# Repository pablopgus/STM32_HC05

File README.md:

# STM32_HC05
This is a PCB board designed in KiCAD which implements a STM32F746VGT6 microcontroller exposing the following pins and internal connections. All of the GPIO pins support timer peripheral output, for a more detailed view of the potential PIN function, check the STM32F7 datasheet using name as a reference. Please read [STM32F7 Reference page](https://www.st.com/en/microcontrollers-microprocessors/stm32f7-series.html) and [Getting Started Guide](https://www.st.com/resource/en/user_manual/dm00180213-getting-started-with-stm32cubef7-mcu-package-for-stm32f7-series-stmicroelectronics.pdf).

This board includes a [HC-05 Bluetooth module](https://components101.com/wireless/hc-05-bluetooth-module)  which exposes a serial port interface over bluetooth as a direct link with the microcontroller. The bluetooth module is switched on/off with a transistor switch controlled by a microcontroller pin. 

## Board Design

## Pinout

## Pin Function

| Name            | Pin     | Extra Functions   |
| :-------------: |:-------:| :-------------:   |
| PA0             | 22      | ADC0, UART4_TX, USART2_CTS |
| PA1             | 23      | ADC1, UART4_RX, USART2_RTS |
| PA2             | 24      | ADC2, USART2_TX            |
| PA3             | 25      | ADC3, USART2_RX            |
| PA4             | 28      | ADC4, USART2_CLK           |
| PA5             | 29      | ADC5, SPI1_CLK             |
| PA6             | 30      | ADC6, SPI1_MISO            |
| PA7             | 31      | ADC7, SPI1_MOSI            |
| PB0             | 34      | ADC8                       |
| PB1             | 35      | ADC9                       |
| PB10            | 46      | I2C2_CLK                   |
| PB11            | 47      | I2C2_SDA                   |
| PD8             | 55      | USART3_TX                  |
| PD9             | 56      | USART3_RX                  |
| PD10            | 57      | USART3_CLK                 |
| PD11            | 58      | USART3_CTS                 |
| PD12            | 59      | USART3_RTS                 |
| PD13            | 60      |                            |
| PD14            | 61      |                            |
| PD15            | 62      |                            |
| PD0             | 81      | Green LED                  |
| PD1             | 82      | Red LED                    |
| PD2             | 83      | Blue LED                   |
| PD3             | 84      | Orange LED                 |
| PD4             | 85      | Yellow LED                 |
| PC6             | 63      | HC-05 UART RX              |
| PC7             | 64      | HC-05 UART TX              |
| PC8             | 65      | HC-05 BT KEY               |
| PE12            | 42      | Bluetooth Enable           |

## Programming Interface
The programming and power port is located on the upper left section of the board. The flashing debugging must be performed using a ST-Link/v2 debugger or STM32FX evaluation board (Discovery, Nucleo, etc ...). LEDs are connected to GPIO (PD0-4), bluetooth module is connected to UART6 port and the bluetooth module on/off actuation is driven by GPIO PE12. Further information on programming and the specific pin functions can be found on the STM32F7 datasheet, and the HC-05 bluetooth module reference guide.

# Code Examples
The following 4 files form the required interface to program and operate the Bluetooth module via the UART peripheral of the STM32F7.
## bluetooth.h
```C
#ifndef __bluetooth_H
#define __bluetooth_H
#ifdef __cplusplus
 extern "C" {
#endif

/* Includes ------------------------------------------------------------------*/
#include "stm32f7xx_hal.h"
#include "stdlib.h"
#include <stdio.h>
#include <string.h>
#include "gpio.h"

void BT_isAlive(void);
void BT_setNameMixcell(void);
void BT_clearPaired(void);
void BT_setMaster(void);
void BT_setSlave(void);
void BT_setCOM(void);
void BT_Reset(void);	
void BT_Restore(void);	
void BT_SendTest(void);
void BT_CMode(void);
void BT_Init_UART(void);
	 
#ifdef __cplusplus
}
#endif
#endif /*__ bluetooth_H */
```
## bluetooth.c
```C
#include "bluetooth.h"

extern UART_HandleTypeDef UART;

extern char data_rx[32];
extern char rx_data[8];			/* Buffer used for UART */

void BT_isAlive(void)
{
	char data_tx[4] = "AT\r\n";
	memset(data_rx, 0x00, 32);
	HAL_UART_Transmit(&UART, (uint8_t *) data_tx, 4, 1000);
	HAL_UART_Receive(&UART, (uint8_t *) data_rx, 24, 1000);
}

void BT_setName(void)
{
	// TODO Set Bluetooth name: MY_NAME.
	char data_tx[17] = "AT+NAME=MY_NAME\r\n";
	memset(data_rx, 0x00, 32);
	HAL_UART_Transmit(&UART, (uint8_t *) data_tx, 17, 500);
	HAL_UART_Receive(&UART, (uint8_t *) data_rx, 24, 500);
}

void BT_setMaster(void)
{
	char data_tx[11] = "AT+ROLE=1\r\n";
	memset(data_rx, 0x00, 32);
	HAL_UART_Transmit(&UART, (uint8_t *) data_tx, 11, 500);
	HAL_UART_Receive(&UART, (uint8_t *) data_rx, 24, 500);
}

void BT_setSlave(void)
{
	char data_tx[11] = "AT+ROLE=0\r\n";
	memset(data_rx, 0x00, 32);
	HAL_UART_Transmit(&UART, (uint8_t *) data_tx, 11, 500);
	HAL_UART_Receive(&UART, (uint8_t *) data_rx, 24, 500);
}

void BT_Reset(void)
{
	char data_tx[10] = "AT+RESET\r\n";
	memset(data_rx, 0x00, 32);
	HAL_UART_Transmit(&UART, (uint8_t *) data_tx, 10, 500);
	HAL_UART_Receive(&UART, (uint8_t *) data_rx, 24, 500);
}

void BT_Restore(void)
{
	char data_tx[9] = "AT+ORGL\r\n";
	memset(data_rx, 0x00, 32);
	HAL_UART_Transmit(&UART, (uint8_t *) data_tx, 9, 500);
	HAL_UART_Receive(&UART, (uint8_t *) data_rx, 32, 500);
}

void BT_clearPaired(void)
{
	char data_tx[10] = "AT+RMAAD\r\n";
	memset(data_rx, 0x00, 32);
	HAL_UART_Transmit(&UART, (uint8_t *) data_tx, 10, 500);
	HAL_UART_Receive(&UART, (uint8_t *) data_rx, 24, 500);
}

void BT_setCOM(void)
{
	char data_tx[20] = "AT+UART=115200,0,0\r\n";
	memset(data_rx, 0x00, 32);
	HAL_UART_Transmit(&UART, (uint8_t *) data_tx, 20, 500);
	HAL_UART_Receive(&UART, (uint8_t *) data_rx, 24, 500);
}
```
## usart.h
```C
/**
  ******************************************************************************
  * File Name          : UART.h
  * Date               : 13/04/2015 14:34:07
  * Description        : This file provides code for the configuration
  *                      of the USART instances.
  ******************************************************************************
  *
  * COPYRIGHT(c) 2015 STMicroelectronics
  *
  * Redistribution and use in source and binary forms, with or without modification,
  * are permitted provided that the following conditions are met:
  *   1. Redistributions of source code must retain the above copyright notice,
  *      this list of conditions and the following disclaimer.
  *   2. Redistributions in binary form must reproduce the above copyright notice,
  *      this list of conditions and the following disclaimer in the documentation
  *      and/or other materials provided with the distribution.
  *   3. Neither the name of STMicroelectronics nor the names of its contributors
  *      may be used to endorse or promote products derived from this software
  *      without specific prior written permission.
  *
  * THIS SOFTWARE IS PROVIDED BY THE COPYRIGHT HOLDERS AND CONTRIBUTORS "AS IS"
  * AND ANY EXPRESS OR IMPLIED WARRANTIES, INCLUDING, BUT NOT LIMITED TO, THE
  * IMPLIED WARRANTIES OF MERCHANTABILITY AND FITNESS FOR A PARTICULAR PURPOSE ARE
  * DISCLAIMED. IN NO EVENT SHALL THE COPYRIGHT HOLDER OR CONTRIBUTORS BE LIABLE
  * FOR ANY DIRECT, INDIRECT, INCIDENTAL, SPECIAL, EXEMPLARY, OR CONSEQUENTIAL
  * DAMAGES (INCLUDING, BUT NOT LIMITED TO, PROCUREMENT OF SUBSTITUTE GOODS OR
  * SERVICES; LOSS OF USE, DATA, OR PROFITS; OR BUSINESS INTERRUPTION) HOWEVER
  * CAUSED AND ON ANY THEORY OF LIABILITY, WHETHER IN CONTRACT, STRICT LIABILITY,
  * OR TORT (INCLUDING NEGLIGENCE OR OTHERWISE) ARISING IN ANY WAY OUT OF THE USE
  * OF THIS SOFTWARE, EVEN IF ADVISED OF THE POSSIBILITY OF SUCH DAMAGE.
  *
  ******************************************************************************
  */
/* Define to prevent recursive inclusion -------------------------------------*/
#ifndef __usart_H
#define __usart_H
#ifdef __cplusplus
 extern "C" {
#endif

/* Includes ------------------------------------------------------------------*/
#include "stm32f7xx_hal.h"
#include "adc.h"
#include "stdlib.h"
#include "bluetooth.h"
	 
void MX_USART_UART_Init(void);
void HAL_UART_MspInit(UART_HandleTypeDef* huart);
void HAL_UART_MspDeInit(UART_HandleTypeDef* huart);
void receive_UART_action(void);
void send_UART_copy(void);
void send_back(char rx_data[8]);
void send_alive(void);

/* HC-05 BT driver. */
void BT_Config(void);
void BT_UART(void);
void send_data(void);

#ifdef __cplusplus
}
#endif
#endif /*__ usart_H */

/**
  * @}
  */

/**
  * @}
  */

/************************ (C) COPYRIGHT STMicroelectronics *****END OF FILE****/
```
## usart.c
```C
#include "usart.h"
#include "gpio.h"
#include <stdio.h>
#include <math.h>
#include "stdlib.h"
#include <string.h>

UART_HandleTypeDef UART;

char data_rx[32] = "";
extern char rx_data[8];			/* Buffer used for UART */
extern uint16_t INFO_TO_SEND[1024]; 	/* Buffer used for ADC */

/* USART6 init function */
void MX_USART_UART_Init(void)
{
  UART.Instance = USART6;
  UART.Init.BaudRate = 38400;
	UART.Init.WordLength = UART_WORDLENGTH_8B;
  UART.Init.StopBits = UART_STOPBITS_1;
  UART.Init.Parity = UART_PARITY_NONE;
  UART.Init.Mode = UART_MODE_TX_RX;
  UART.Init.HwFlowCtl = UART_HWCONTROL_NONE;
  UART.Init.OverSampling = UART_OVERSAMPLING_16;
	UART.Init.OneBitSampling = UART_ONEBIT_SAMPLING_DISABLED;
  UART.AdvancedInit.AdvFeatureInit = UART_ADVFEATURE_NO_INIT;
  HAL_UART_Init(&UART);
}

void HAL_UART_MspInit(UART_HandleTypeDef* huart)
{

  GPIO_InitTypeDef GPIO_InitStruct;
  if(huart->Instance==USART6)
  {
  /* USER CODE BEGIN USART_MspInit 0 */

  /* USER CODE END USART_MspInit 0 */
    /* Peripheral clock enable */
		__GPIOC_CLK_ENABLE();
    __USART6_CLK_ENABLE();
  
    /**USART6 GPIO Configuration    
    PC6     ------> USART6_TX
    PC7     ------> USART6_RX 
    */
    GPIO_InitStruct.Pin = GPIO_PIN_6|GPIO_PIN_7;
    GPIO_InitStruct.Mode = GPIO_MODE_AF_PP;
    GPIO_InitStruct.Pull = GPIO_PULLUP;
    GPIO_InitStruct.Speed = GPIO_SPEED_HIGH;
    GPIO_InitStruct.Alternate = GPIO_AF8_USART6;
    HAL_GPIO_Init(GPIOC, &GPIO_InitStruct);
		
  /* System interrupt init*/
    HAL_NVIC_SetPriority(USART6_IRQn, 0, 0);
    HAL_NVIC_EnableIRQ(USART6_IRQn);
  /* USER CODE BEGIN USART6_MspInit 1 */

  /* USER CODE END USART6_MspInit 1 */
  }

}

void HAL_UART_MspDeInit(UART_HandleTypeDef* huart)
{

  if(huart->Instance==USART6)
  {
  /* USER CODE BEGIN USART6_MspDeInit 0 */

  /* USER CODE END USART6_MspDeInit 0 */
    /* Peripheral clock disable */
    __USART6_CLK_DISABLE();
  
    /**USART6 GPIO Configuration    
    PC6     ------> USART6_TX
    PC7     ------> USART6_RX 
    */
    HAL_GPIO_DeInit(GPIOC, GPIO_PIN_6|GPIO_PIN_7);

    /* Peripheral interrupt DeInit*/
    HAL_NVIC_DisableIRQ(USART6_IRQn);

  /* USER CODE BEGIN USART6_MspDeInit 1 */

  /* USER CODE END USART6_MspDeInit 1 */
  }

}

/* USER CODE BEGIN 1 */
void BT_Init_UART()
{
	BT_UART();
}

void BT_Config(void)
{
	BT_Reset();
	HAL_Delay(1000);
	BT_isAlive();
	HAL_Delay(1000);
	BT_Restore();
	HAL_Delay(1000);
	BT_setName();
	HAL_Delay(1000);
	BT_setCOM();
	HAL_Delay(1000);
	BT_clearPaired();
	HAL_Delay(1000);
}

void BT_SendTest(void)
{
	BT_isAlive();
}

void BT_UART(void)
{
	HAL_UART_DeInit(&UART);
	
  UART.Instance = USART6;
  UART.Init.BaudRate = 115200;
  UART.Init.WordLength = UART_WORDLENGTH_8B;
  UART.Init.StopBits = UART_STOPBITS_1;
  UART.Init.Parity = UART_PARITY_NONE;
  UART.Init.Mode = UART_MODE_TX_RX;
  UART.Init.HwFlowCtl = UART_HWCONTROL_NONE;
  UART.Init.OverSampling = UART_OVERSAMPLING_16;
  HAL_UART_Init(&UART);
}

/* TX SECTION */
void send_alive()
{
	char data_tx[9] = "SM_ALIVE\n";
	memset(data_rx, 0x00, 32);
	HAL_UART_Transmit(&UART, (uint8_t *) data_tx, 9, 1000);
	receive_UART_action();
}

void send_data(void)
{
	// TODO: INFO_TO_SEND would be the char array to be send. 
	uint8_t * data;
	HAL_UART_Transmit(&UART, (uint8_t *)(INFO_TO_SEND), 16384, 10000);
}

void send_back(char rx_data[8])
{
		HAL_UART_Transmit(&UART, (uint8_t *)rx_data, 8, 1000);		
}

/* RX SECTION */
void receive_UART_action()
{
	int i = 0;
	while (i < 8)
	{
		rx_data[i] = 0x00;
		i++;
	}
	HAL_UART_Receive_IT(&UART, (uint8_t *)rx_data, 8);
}

void HAL_UART_RxCpltCallback(UART_HandleTypeDef *huart)
{
		// TODO: Reception complete.
}
```

# Success Stories
- [Sensing Cell-Culture Assays with Low-Cost Circuitry](https://www.nature.com/articles/s41598-018-27295-3)
- [An Empirical-Mathematical Approach for Calibration and Fitting Cell-Electrode Electrical Models in Bioimpedance Tests](https://www.mdpi.com/1424-8220/18/7/2354)
- [Remote Cell Growth Sensing Using Self-Sustained Bio-Oscillations](https://www.mdpi.com/1424-8220/18/8/2550)
- [Data-Analytics Modeling of Electrical Impedance Measurements for Cell Culture Monitoring](https://www.mdpi.com/1424-8220/19/21/4639)
- [Electrical Modeling of the Growth and Differentiation of Skeletal Myoblasts Cell Cultures for Tissue Engineering](https://www.mdpi.com/1424-8220/20/11/3152)

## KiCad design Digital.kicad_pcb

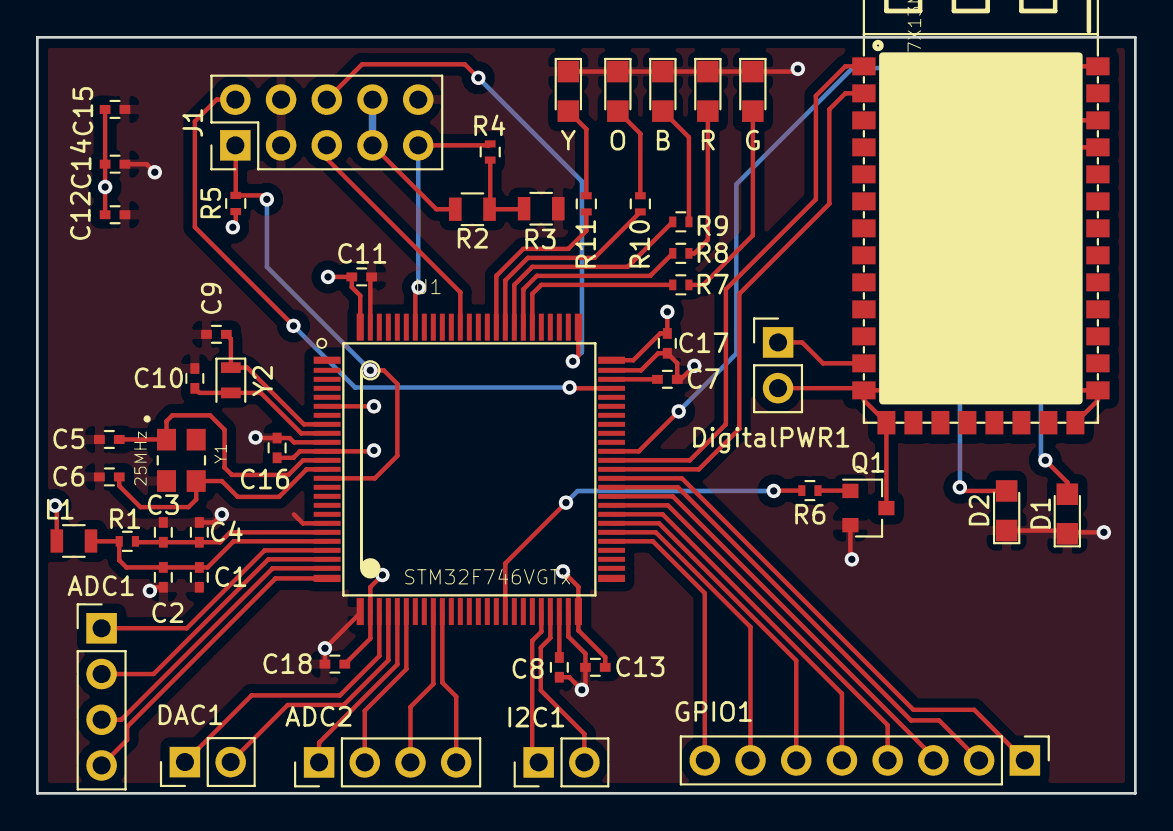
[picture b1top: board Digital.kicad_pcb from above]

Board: 4 copper layers, 61.0 x 42.0 mm, 49 parts (0 on the bottom side), 54 nets.

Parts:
ADC1, ADC2: Conn_01x04; Pin_Header_Straight_1x04_Pitch2.54mm
B: LED; LED_0805
C1, C3: 1uF; C_0402
C2, C4, C11, C12, C13, C14, C15, C16, C17, C18: 100nF; C_0402
C5, C6: 22nF; C_0402
C7, C8: 2.2uF; C_0402
C9, C10: 6pF; C_0402
D1, D2: LED; LED_0805
DAC1: Conn_01x02; Pin_Header_Straight_1x02_Pitch2.54mm
DigitalPWR1: Conn_01x02; Pin_Header_Straight_1x02_Pitch2.54mm
G: LED; LED_0805
GPIO1: Conn_01x08; Pin_Header_Straight_1x08_Pitch2.54mm
I2C1: Conn_01x02; Pin_Header_Straight_1x02_Pitch2.54mm
J1: Conn_02x05_Odd_Even_MountingPin; Pin_Header_Straight_2x05_Pitch2.54mm
L1: INDUCTOR; L_0805
O: LED; LED_0805
Q1: Q_NMOS_GSD; SOT-23
R: LED; LED_0805
R1, R7, R8, R9, R10, R11: 47; R_0402
R2, R3: 33K; R_0805
R4, R5, R6: 33K; R_0402
U1: STM32F746VGTx; LQFP100
U2: MOUDLE-BLUETOOTH-HC-05(34P-27X13MM); HC05
Y: LED; LED_0805
Y1: 25MHz; OSCCC320X250X60N
Y2: 32kHz; Crystal_SMD_2012-2pin_2.0x1.2mm

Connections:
+3V3: C11.2, C12.2, C13.2, C14.2, C15.2, C16.2, C17.2, C18.2, DigitalPWR1.1, J1.7, J1.8, L1.1, R2.2, R5.1, U1.6, U1.11, U1.27, U1.50, U1.75, U1.100, U2.12
BOOT0: J1.9, R4.2, U1.94
BT_KEY: U1.65, U2.34
DIGITAL_ENABLE: R6.2, U1.42
GND: B.1, C1.2, C2.2, C3.1, C4.1, C5.1, C6.1, C7.1, C8.1, C9.2, C10.2, C11.1, C12.1, C13.1, C14.1, C15.1, C16.1, C17.1, C18.1, D1.1, D2.1, G.1, J1.3, J1.4, J1.10, O.1, Q1.2, R.1, R3.2, U1.10, U1.19, U1.26, U1.49, U1.74, U1.99, Y.1, Y1.2
GNDPWR: DigitalPWR1.2, Q1.3, U2.13, U2.14, U2.21, U2.22
NRST: J1.1, R5.2, U1.14
unnamed: ADC1.1, U1.22
unnamed: ADC1.2, U1.23
unnamed: ADC1.3, U1.24
unnamed: ADC1.4, U1.25
unnamed: ADC2.1, U1.30
unnamed: ADC2.2, U1.31
unnamed: ADC2.3, U1.34
unnamed: ADC2.4, U1.35
unnamed: B.2, R9.2
unnamed: C3.2, C4.2, R1.1, U1.20
unnamed: C5.2, U1.12, Y1.1
unnamed: C6.2, U1.13, Y1.3
unnamed: C7.2, U1.73
unnamed: C8.2, U1.48
unnamed: C9.1, U1.8, Y2.1
unnamed: C10.1, U1.9, Y2.2
unnamed: D1.2, U2.32
unnamed: D2.2, U2.31
unnamed: DAC1.1, U1.28
unnamed: DAC1.2, U1.29
unnamed: GPIO1.1, U1.62
unnamed: GPIO1.2, U1.61
unnamed: GPIO1.3, U1.60
unnamed: GPIO1.4, U1.59
unnamed: GPIO1.5, U1.58
unnamed: GPIO1.6, U1.57
unnamed: GPIO1.7, U1.56
unnamed: GPIO1.8, U1.55
unnamed: G.2, R7.2
unnamed: I2C1.1, U1.46
unnamed: I2C1.2, U1.47
unnamed: O.2, R10.2
unnamed: Q1.1, R6.1
unnamed: R2.1, R3.1, R4.1
unnamed: R7.1, U1.81
unnamed: R8.1, U1.82
unnamed: R.2, R8.2
unnamed: R9.1, U1.83
unnamed: R10.1, U1.84
unnamed: R11.1, U1.85
unnamed: R11.2, Y.2
SWCLK: J1.6, U1.76
SWDIO: J1.2, U1.72
SWO: J1.5, U1.89
UART_RX: U1.63, U2.2
UART_TX: U1.64, U2.1
VREF: C1.1, C2.1, L1.2, R1.2, U1.21

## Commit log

2019-03-08 Initial Commit. Alpha version.
2019-03-11 Footprint changed in Y1
2021-03-01 Set theme jekyll-theme-slate
2021-03-01 Images included.
2021-03-01 Rename README.md to index.md
